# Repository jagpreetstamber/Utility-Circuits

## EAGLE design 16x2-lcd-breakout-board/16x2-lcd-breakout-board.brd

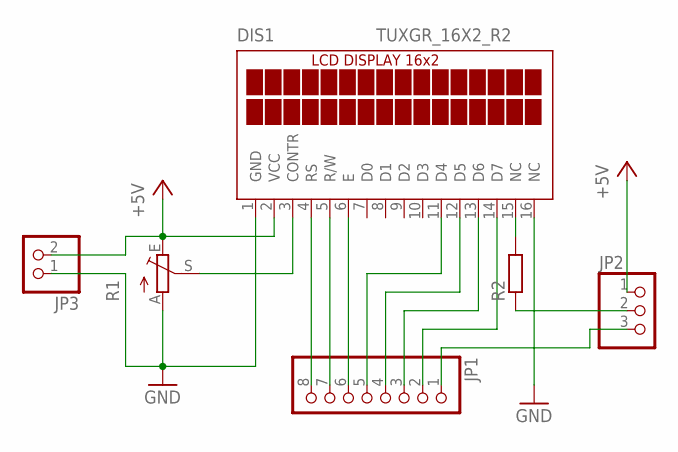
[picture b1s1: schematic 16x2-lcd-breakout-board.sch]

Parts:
DIS1: TUXGR_16X2_R2
JP1: PINHD-1X8; 1X08
JP2: PINHD-1X3; 1X03
JP3: PINHD-1X2; 1X02
R1: TRIM_EU-S63P; S63P
R2: R-EU_0207/10; 0207/10

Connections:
+5V: DIS1.2 (VCC), JP2.1, JP3.2, R1.E
GND: DIS1.1 (GND), DIS1.16 (NC), JP3.1, R1.A
unnamed: DIS1.3 (CONTR), R1.S
unnamed: DIS1.4 (RS), JP1.8
unnamed: DIS1.5 (R/W), JP1.7
unnamed: DIS1.6 (E), JP1.6
unnamed: DIS1.11 (D4), JP1.5
unnamed: DIS1.12 (D5), JP1.4
unnamed: DIS1.13 (D6), JP1.3
unnamed: DIS1.14 (D7), JP1.2
unnamed: DIS1.15 (NC), R2.2
unnamed: JP1.1, JP2.3
unnamed: JP2.2, R2.1

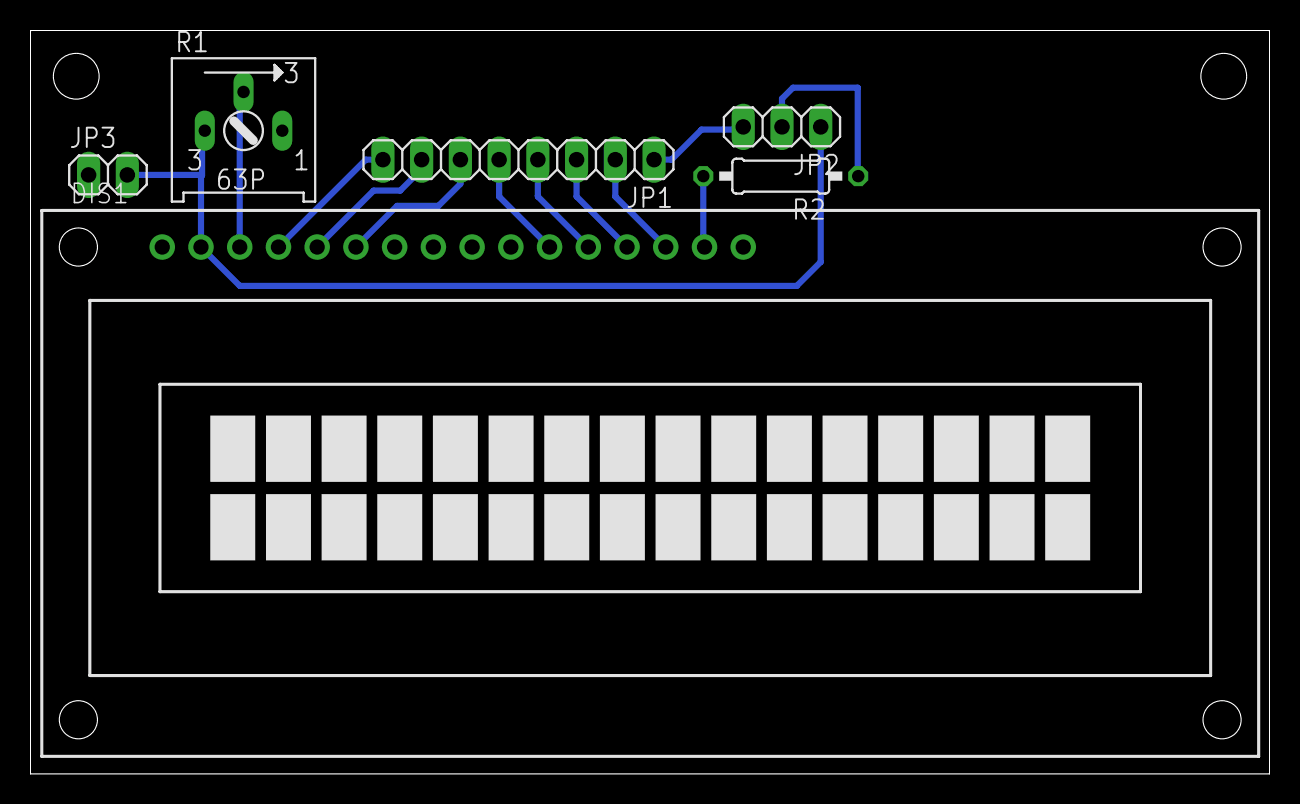
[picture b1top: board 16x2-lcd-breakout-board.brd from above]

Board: 2 copper layers, 81.2 x 48.8 mm, 6 parts (0 on the bottom side), 13 nets.

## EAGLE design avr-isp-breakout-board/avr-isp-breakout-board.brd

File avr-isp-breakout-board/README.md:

# Breakout board for AVR USB ASP ISP

This breakout board can be used for below:

- Program Arduino using 6 pin ISP header
- Plug USB asp to breadboard
- 5 pinhead for ISP of any AVR

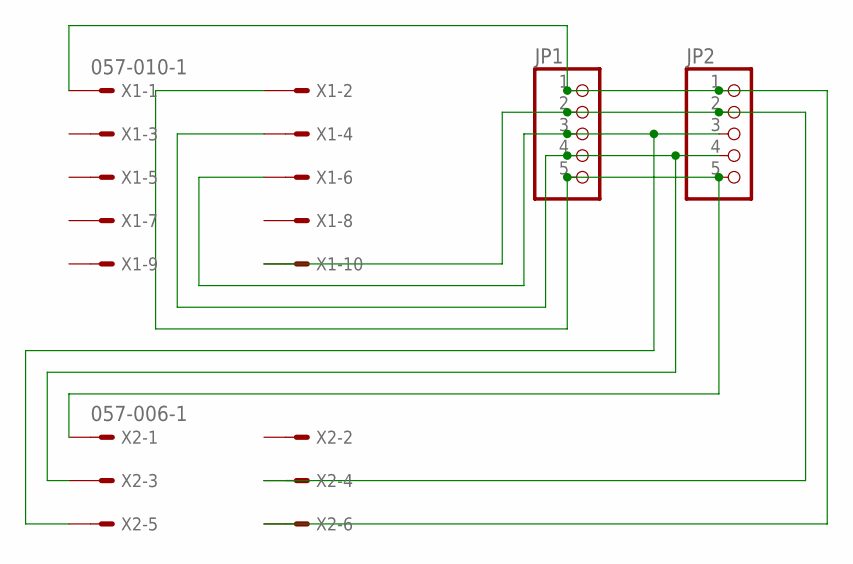
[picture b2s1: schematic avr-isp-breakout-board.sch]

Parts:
JP1, JP2: PINHD-1X5; 1X05
X1: 057-010-1
X2: 057-006-1

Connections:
GND: JP1.1, JP2.1, X1.1, X2.6
MISO: JP1.5, JP2.5, X1.2, X2.1
MOSI: JP1.2, JP2.2, X1.10, X2.4
RESET: JP1.3, JP2.3, X1.6, X2.5
SCK: JP1.4, JP2.4, X1.4, X2.3

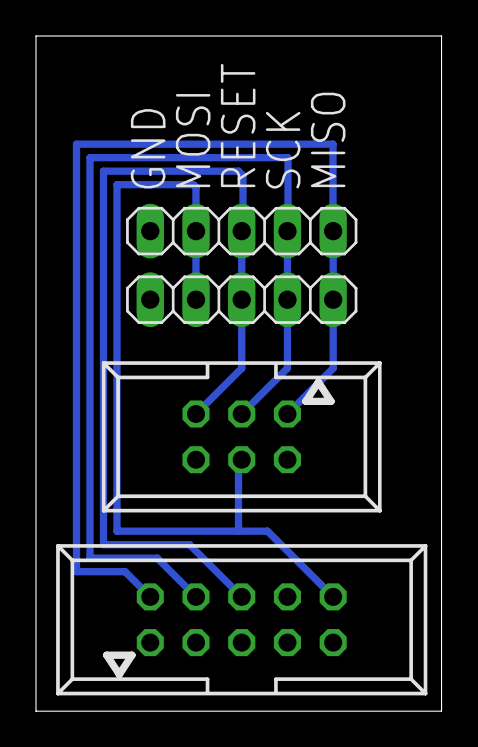
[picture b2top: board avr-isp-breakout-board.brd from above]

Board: 2 copper layers, 22.5 x 37.5 mm, 4 parts (0 on the bottom side), 5 nets.

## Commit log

2016-10-19 AVR ISP Breakout board for arduino and breadboard
2016-10-19 README added
2016-10-22 16x2 LCD breakout board added
